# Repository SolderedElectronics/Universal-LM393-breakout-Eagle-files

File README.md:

# Universal LM393 breakout Eagle Files
## Image

[LDR LM393 breakout(100027)](https://e-radionica.com/en/light-sensor-with-lm393-e-radionica-made.html)
[Vibration sensor LM393 breakout(100031)](https://e-radionica.com/en/vibration-sensor-with-lm393-e-radionica-made.html)
[Raindrop LM393 breakout(100030)](https://e-radionica.com/en/humidity-sensor-with-lm393-e-radionica-made.html)
[Fire sensor LM393 breakout(100028)](https://e-radionica.com/en/fire-sensor-phototransistor-s-lm393-e-radionica-made.html)
[Hall effect LM393 breakout(100029)](https://e-radionica.com/en/hall-effect-sensor-s-lm393-e-radionica-made.html)

## Description and details
Universal LM393 is breakout for different sensors which are connected to the LM393 voltage comapator. According to the setting of the potenciometer and the value of connected sensor, you will get digital HIGH(Vcc) or LOW(0V) at digital output. Analog output is also available. Check schematics for details.

We have made versions of this board with: 
- LDR(light depending resistor)
- vibration sensor
- Hall effect sensor(pads are at the bottom side of PCB)
- Raindrop sensor
- Phototransistor(responses to IR light, can be used to detect fire or sunlight)

## Repository content
This repo contains Cadsoft Eagle .sch and .brd files for Universal LM393 board. It also contains schematic in .pdf created from .sch Eagle file. 
Files have been arranged into folders for navigating between different versions of board. 
Tip: layer 200 shows top silkscreen and layer 208 should be bottom silkscreen. tParts and bParts layers are not used in actual PCB. 

## Docs
- [Universal LM393 breakout sample product] (https://e-radionica.com/en/light-sensor-with-lm393-e-radionica-made.html)

## Board versions
- v1.0 REV A - inital published version 

## License info
This product is open-source. Yay!
For any tech questions, contact us at techsupport@e-radionica.com
If you find an Issue, please open one at GitHub. If you can improve our product, fork us.

e-radionica.com Team.

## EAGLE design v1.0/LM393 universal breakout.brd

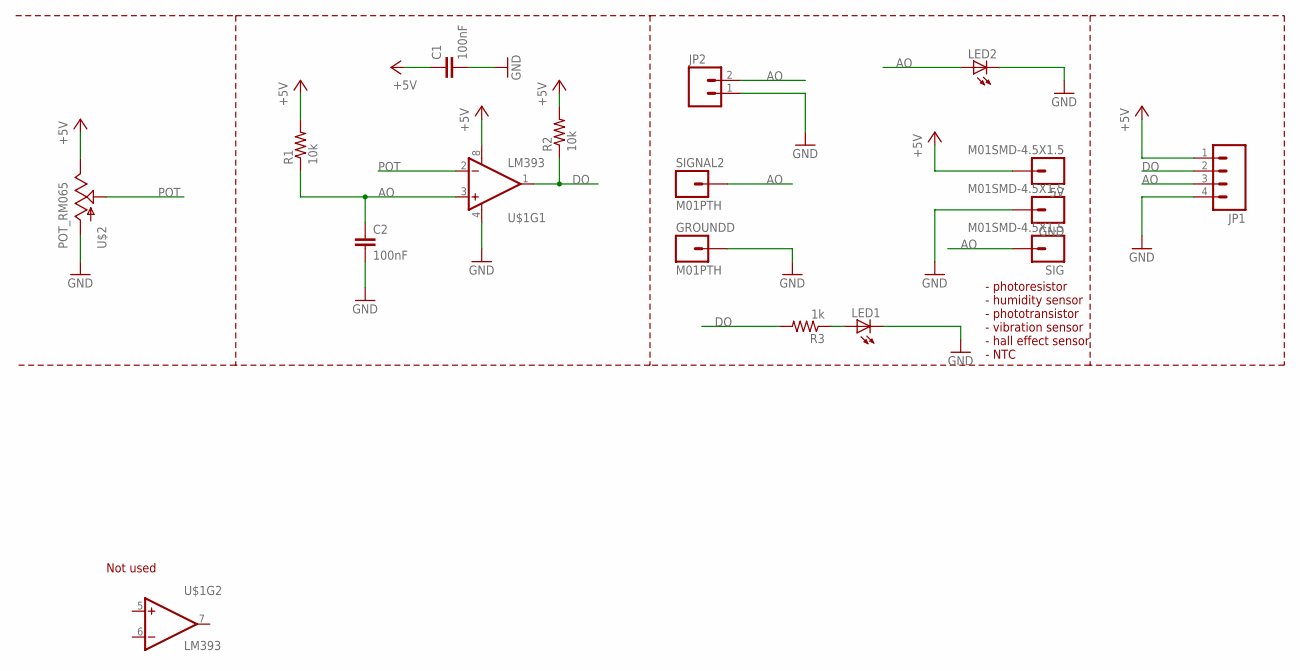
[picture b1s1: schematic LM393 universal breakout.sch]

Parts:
5V: M01SMD-4.5X1.5; PAD-1.5X4.5
C1, C2: 100nF; 0603-CAP
GND: M01SMD-4.5X1.5; PAD-1.5X4.5
GROUNDD: M01PTH; 1X01
JP1: M04PTH; 1X04
JP2: M02PTH; 1X02
LED1: LEDCHIP-LED0805; CHIP-LED0805
LED2: LED5MM
R1, R2: 10k; 0603-RES
R3: 1k; 0603-RES
SIG: M01SMD-4.5X1.5; PAD-1.5X4.5
SIGNAL2: M01PTH; 1X01
U$1: LM393; SO08
U$2: POT_RM065; RM065

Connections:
+5V: 5V.P$1, C1.1, JP1.1, R1.2, R2.2, U$1.8 (V+), U$2.3 (E)
AO: C2.1, JP1.3, JP2.2, LED2.A, R1.1, SIG.P$1, SIGNAL2.1, U$1.3 (+IN)
DO: JP1.2, R2.1, R3.2, U$1.1 (OUT)
GND: C1.2, C2.2, GND.P$1, GROUNDD.1, JP1.4, JP2.1, LED1.C, LED2.K (C), U$1.4 (V-), U$2.1 (A)
unnamed: LED1.A, R3.1
POT: U$1.2 (-IN), U$2.2 (S)

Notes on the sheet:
Not used
- photoresistor - humidity sensor - phototransistor - vibration sensor - hall effect sensor - NTC

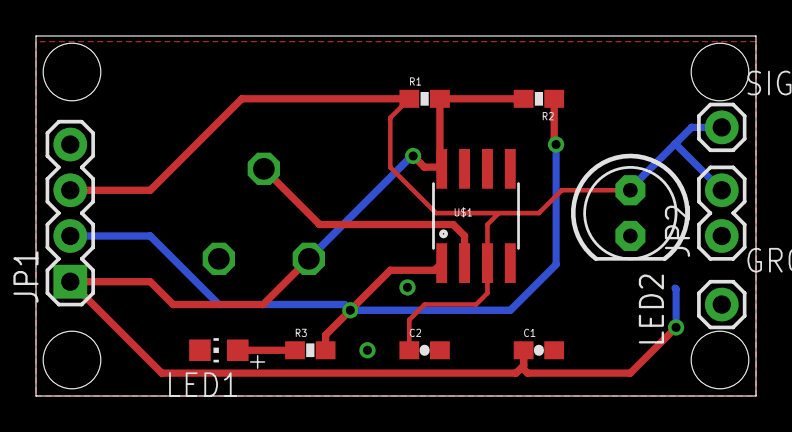
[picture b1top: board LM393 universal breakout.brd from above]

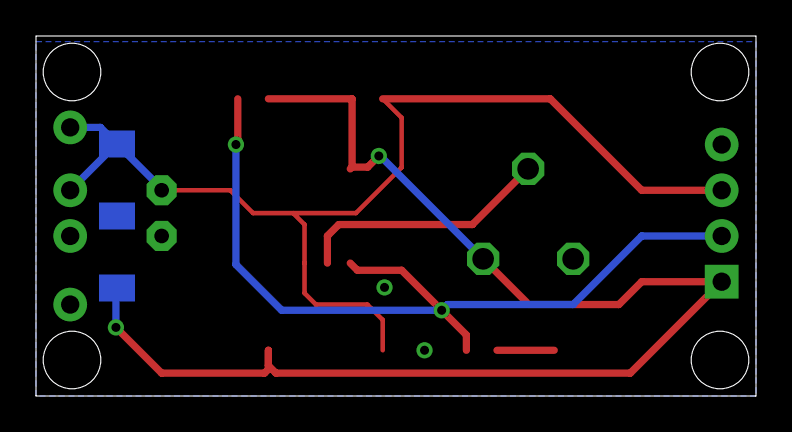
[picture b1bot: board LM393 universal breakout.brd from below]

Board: 2 copper layers, 40.0 x 20.0 mm, 20 parts (3 on the bottom side), 6 nets.

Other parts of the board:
U$3: NOVI_LOGO-4MM
U$4: OSH3MM
U$5: LUDI_LOGO_BACK
U$6: E-RADIONICA.COM_MADE_IN_BACK!

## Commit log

2018-11-26 README update

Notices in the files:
parts and their libraries:
SparkFun: Licensing: CC v3.0 Share-Alike You are welcome to use this library for commercial purposes.
